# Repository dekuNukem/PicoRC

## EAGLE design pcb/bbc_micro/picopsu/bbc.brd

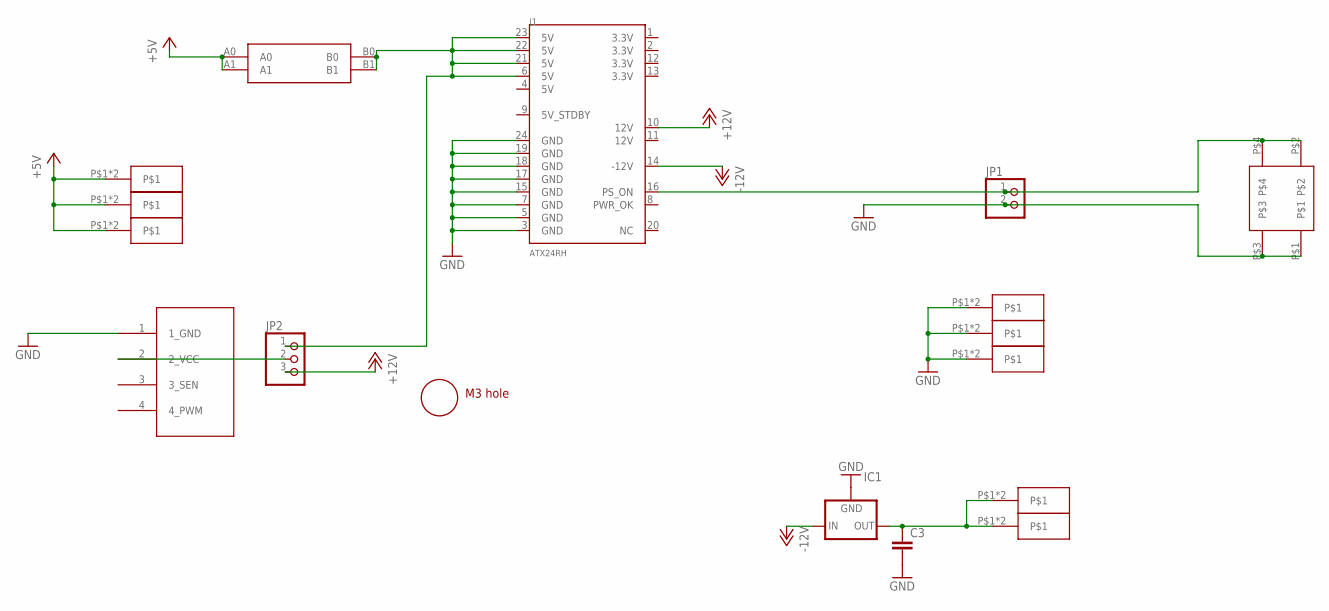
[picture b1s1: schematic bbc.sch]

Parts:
C3: C5/2.5; C5B2.5
IC1: 79XXS
J1: ATX24RH; ATX24_RIGHT_ANGLE
JP1: PINHD-1X2; 1X02
JP2: PINHD-1X3; 1X03
JP3: 4PIN_FAN; 1X04
U$1: CAR_FUSE_HOLDER3IN1; FUSE_HOLDER_3IN1
U$2, U$5, U$6, U$7, U$8, U$9, U$10, U$11: BLADE28; 2.8BLADE
U$3: ROCK_SW; ROCK_SWITCH
U$4: M3_MOUNTING_HOLE; M3_MOUNTING_HOLE_PACK

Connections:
+5V: U$1.A0, U$1.A1, U$6.P$1, U$6.P$2, U$7.P$1, U$7.P$2, U$8.P$1, U$8.P$2
+12V: J1.10 (12V), JP2.3
-12V: IC1.IN, J1.14 (-12V)
GND: C3.2, IC1.GND, J1.3 (GND), J1.5 (GND), J1.7 (GND), J1.15 (GND), J1.17 (GND), J1.18 (GND), J1.19 (GND), J1.24 (GND), JP1.2, JP3.1 (1_GND), U$3.P$1, U$3.P$3, U$9.P$1, U$9.P$2, U$10.P$1, U$10.P$2, U$11.P$1, U$11.P$2
unnamed: JP2.2, JP3.2 (2_VCC)
unnamed: C3.1, IC1.OUT, U$2.P$1, U$2.P$2, U$5.P$1, U$5.P$2
unnamed: J1.16 (PS_ON), JP1.1, U$3.P$2, U$3.P$4
unnamed: J1.6 (5V), J1.21 (5V), J1.22 (5V), J1.23 (5V), JP2.1, U$1.B0, U$1.B1

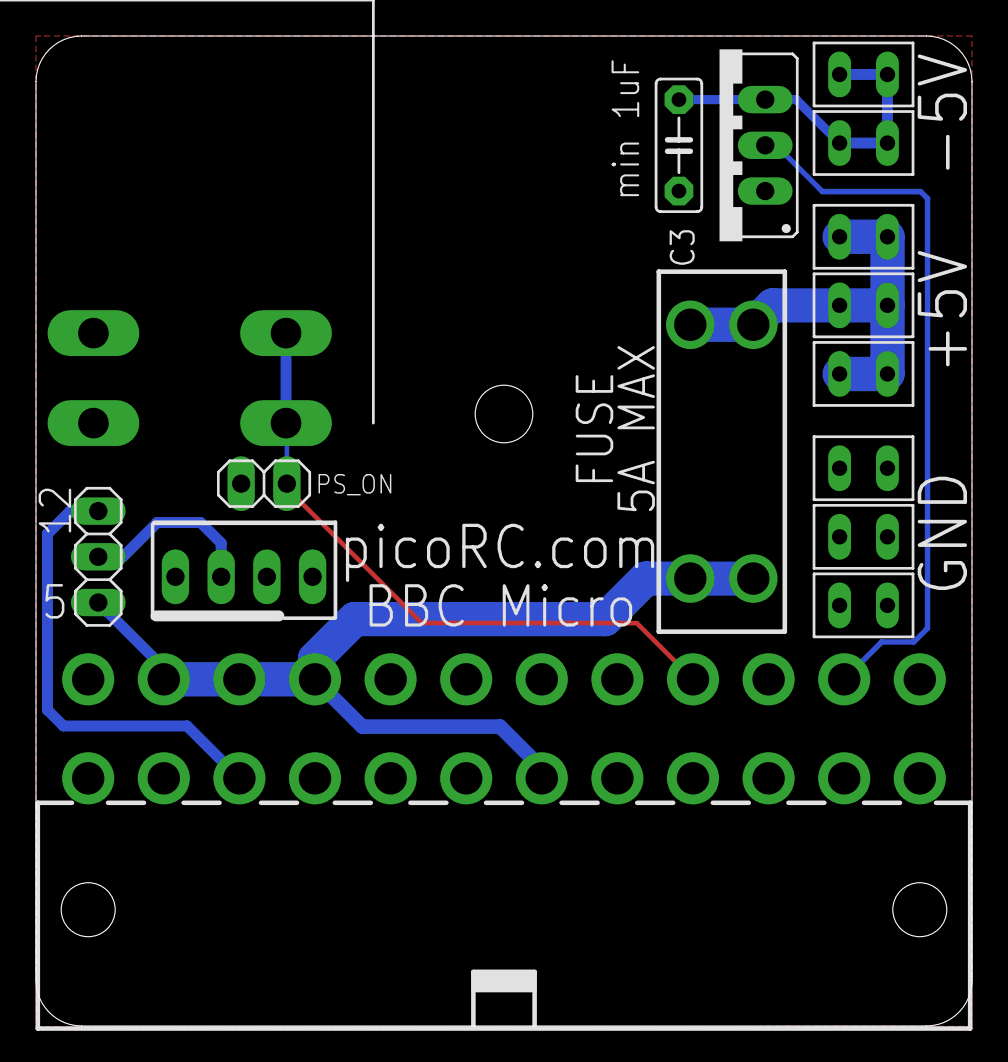
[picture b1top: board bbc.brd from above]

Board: 2 copper layers, 52.0 x 55.0 mm, 17 parts (0 on the bottom side), 8 nets.

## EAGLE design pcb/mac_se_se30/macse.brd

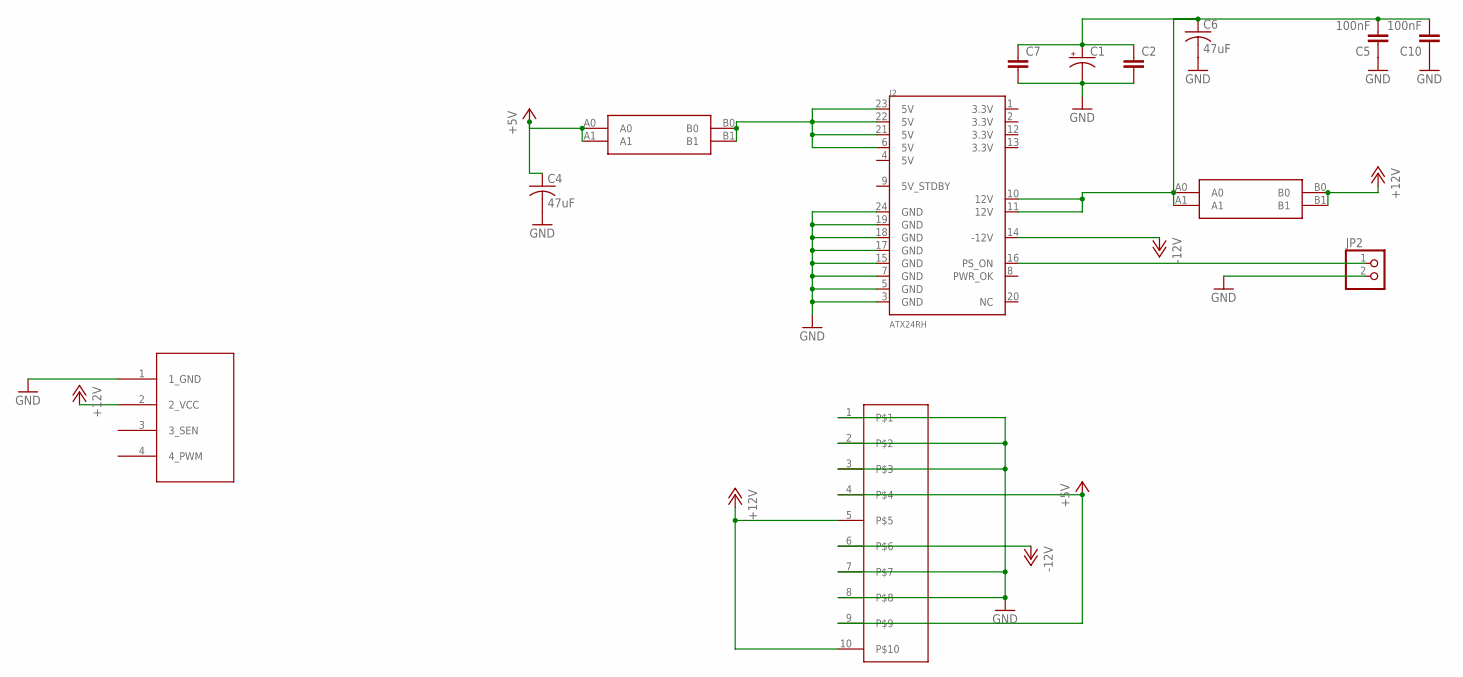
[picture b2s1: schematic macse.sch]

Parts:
C1: CPOL-USE3.5-8; E3,5-8
C2, C7: C5/2.5; C5B2.5
C4, C6: 47uF; C1210
C5, C10: 100nF; 0805@1
J2: ATX24RH; ATX24_RIGHT_ANGLE
JP2: PINHD-1X2/90; 1X02/90
JP3: 4PIN_FAN; 1X04
U$1: MACSE; MACSE_10P_STRAIGHT
U$2, U$8: CAR_FUSE_HOLDER3IN1; FUSE_HOLDER_3IN1

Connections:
+5V: C4.1, U$1.4, U$1.9, U$8.A0, U$8.A1
+12V: JP3.2 (2_VCC), U$1.5, U$1.10, U$2.B0, U$2.B1
-12V: J2.14 (-12V), U$1.6
GND: C1.-, C2.2, C4.2, C5.1, C6.2, C7.2, C10.1, J2.3 (GND), J2.5 (GND), J2.7 (GND), J2.15 (GND), J2.17 (GND), J2.18 (GND), J2.19 (GND), J2.24 (GND), JP2.2, JP3.1 (1_GND), U$1.1, U$1.2, U$1.3, U$1.7, U$1.8
unnamed: J2.16 (PS_ON), JP2.1
unnamed: J2.6 (5V), J2.21 (5V), J2.22 (5V), J2.23 (5V), U$8.B0, U$8.B1
unnamed: C1.+, C2.1, C5.2, C6.1, C7.1, C10.2, J2.10 (12V), J2.11 (12V), U$2.A0, U$2.A1

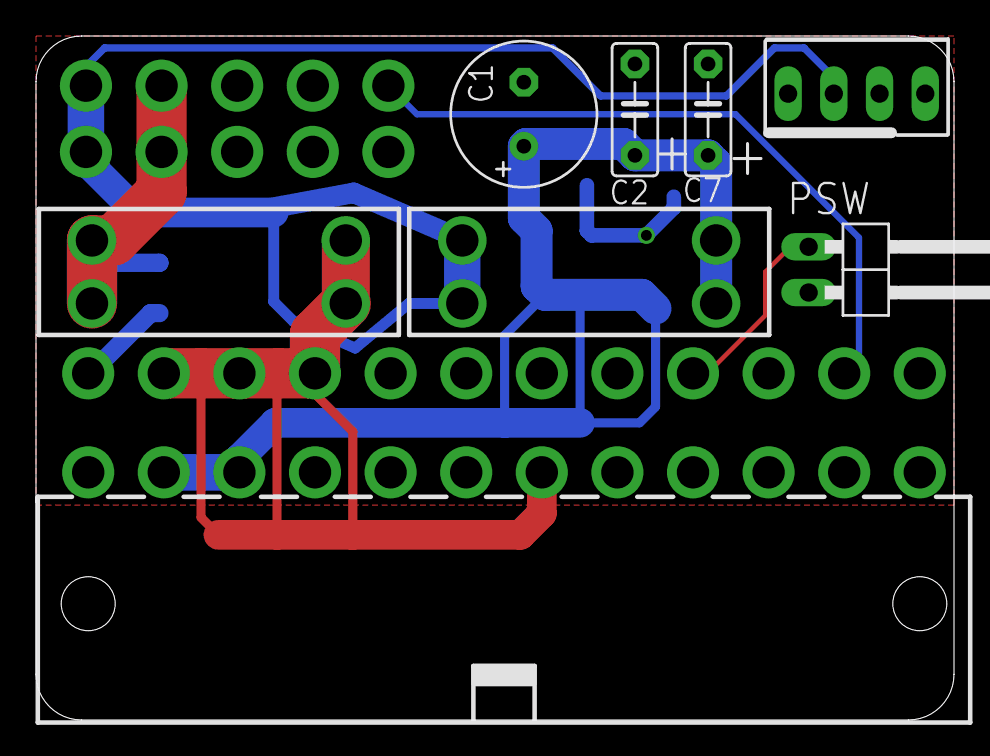
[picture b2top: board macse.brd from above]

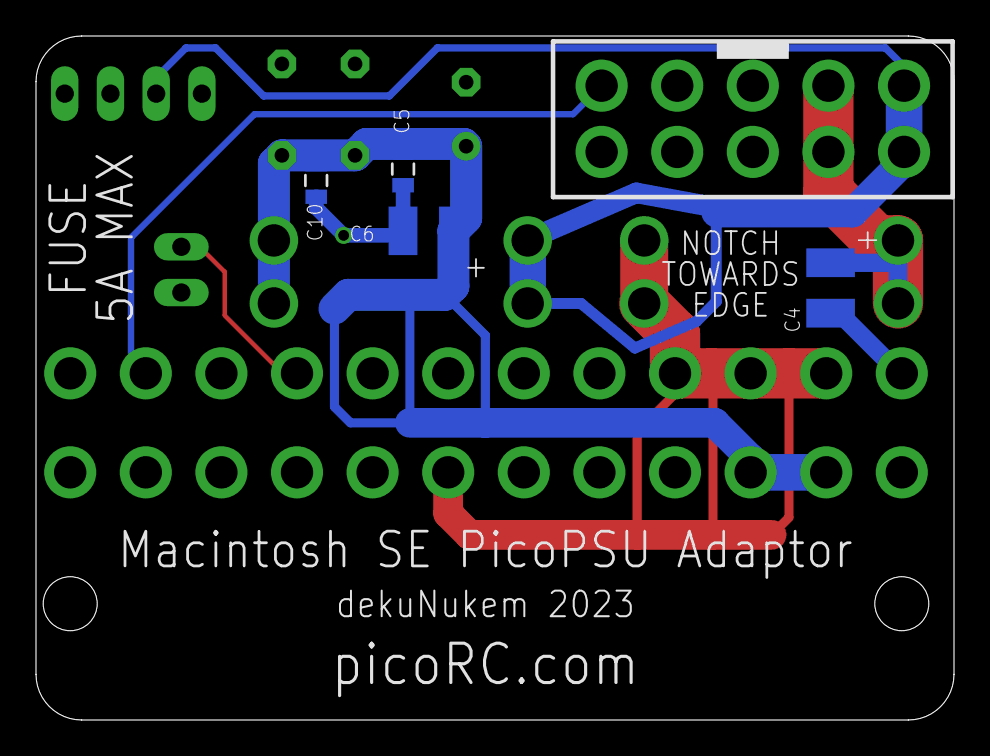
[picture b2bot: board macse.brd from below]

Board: 2 copper layers, 51.0 x 38.0 mm, 13 parts (4 on the bottom side), 7 nets.

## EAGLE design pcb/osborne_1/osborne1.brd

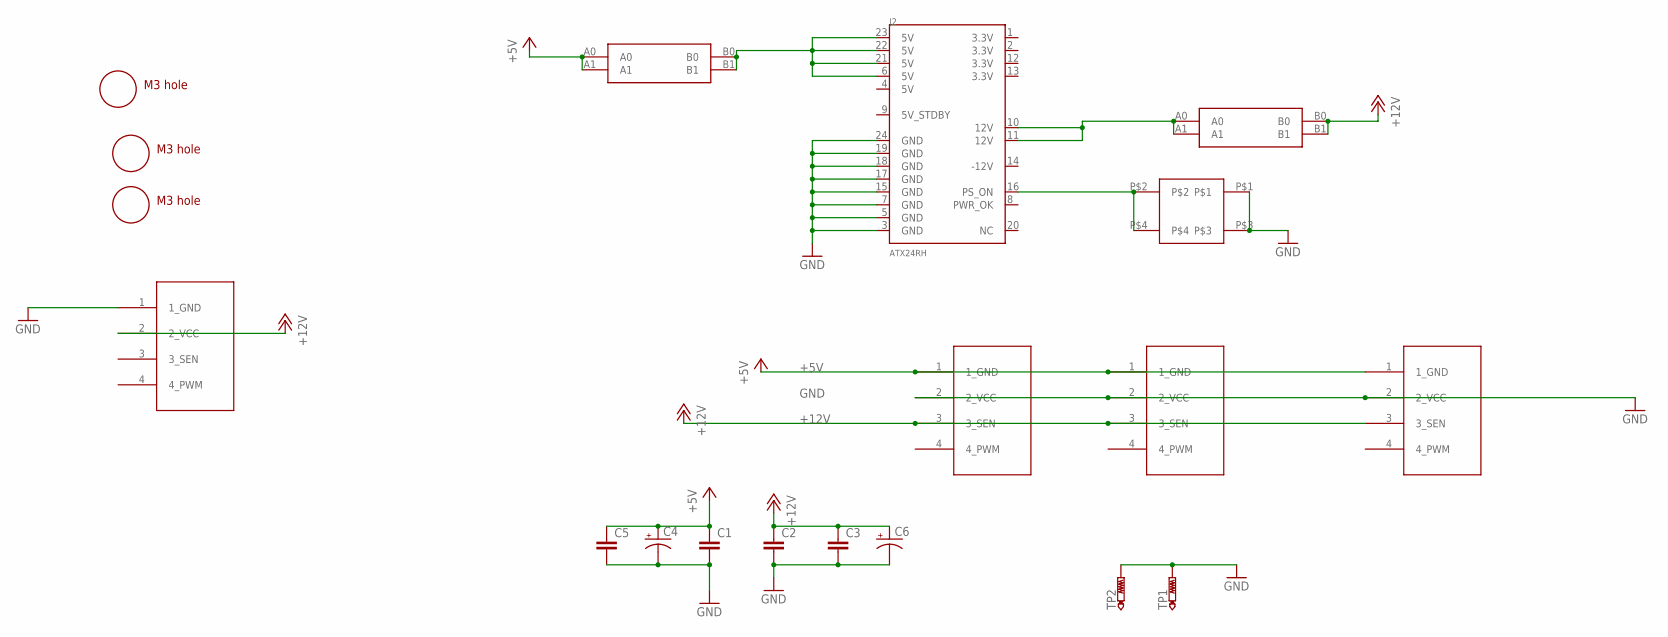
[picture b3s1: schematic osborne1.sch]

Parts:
C1, C2, C3, C5: C5/2.5; C5B2.5
C4, C6: CPOL-USE3.5-8; E3,5-8
J2: ATX24RH; ATX24_RIGHT_ANGLE
JP1, JP2, JP3, JP5: 4PIN_FAN; 1X04
TP1, TP2: PTR1PAD1-17; P1-17
U$1, U$3, U$5: M3_MOUNTING_HOLE; M3_MOUNTING_HOLE_PACK
U$2, U$8: CAR_FUSE_HOLDER3IN1; FUSE_HOLDER_3IN1
U$4: ROCK_SWRSW_VERTICAL; ROCK_SWITCH_VERTICAL

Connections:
+5V: C1.1, C4.+, C5.1, JP1.1 (1_GND), JP2.1 (1_GND), JP5.1 (1_GND), U$8.A0, U$8.A1
+12V: C2.1, C3.1, C6.+, JP1.3 (3_SEN), JP2.3 (3_SEN), JP3.2 (2_VCC), JP5.3 (3_SEN), U$2.B0, U$2.B1
GND: C1.2, C2.2, C3.2, C4.-, C5.2, C6.-, J2.3 (GND), J2.5 (GND), J2.7 (GND), J2.15 (GND), J2.17 (GND), J2.18 (GND), J2.19 (GND), J2.24 (GND), JP1.2 (2_VCC), JP2.2 (2_VCC), JP3.1 (1_GND), JP5.2 (2_VCC), TP1.TP, TP2.TP, U$4.P$1, U$4.P$3
unnamed: J2.16 (PS_ON), U$4.P$2, U$4.P$4
unnamed: J2.6 (5V), J2.21 (5V), J2.22 (5V), J2.23 (5V), U$8.B0, U$8.B1
unnamed: J2.10 (12V), J2.11 (12V), U$2.A0, U$2.A1

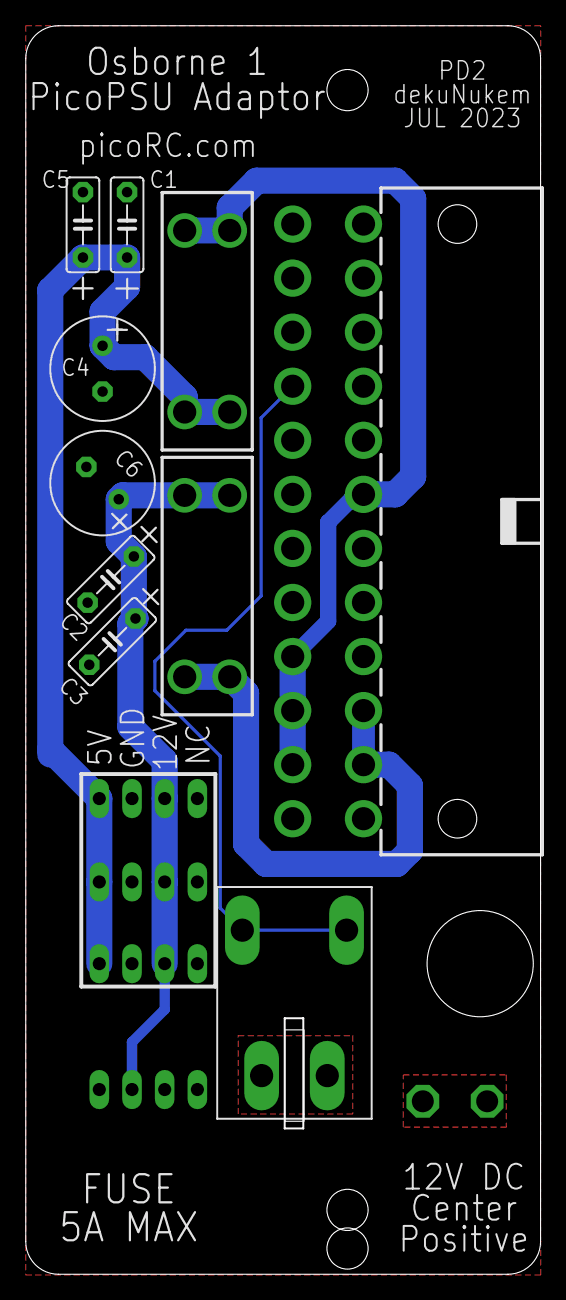
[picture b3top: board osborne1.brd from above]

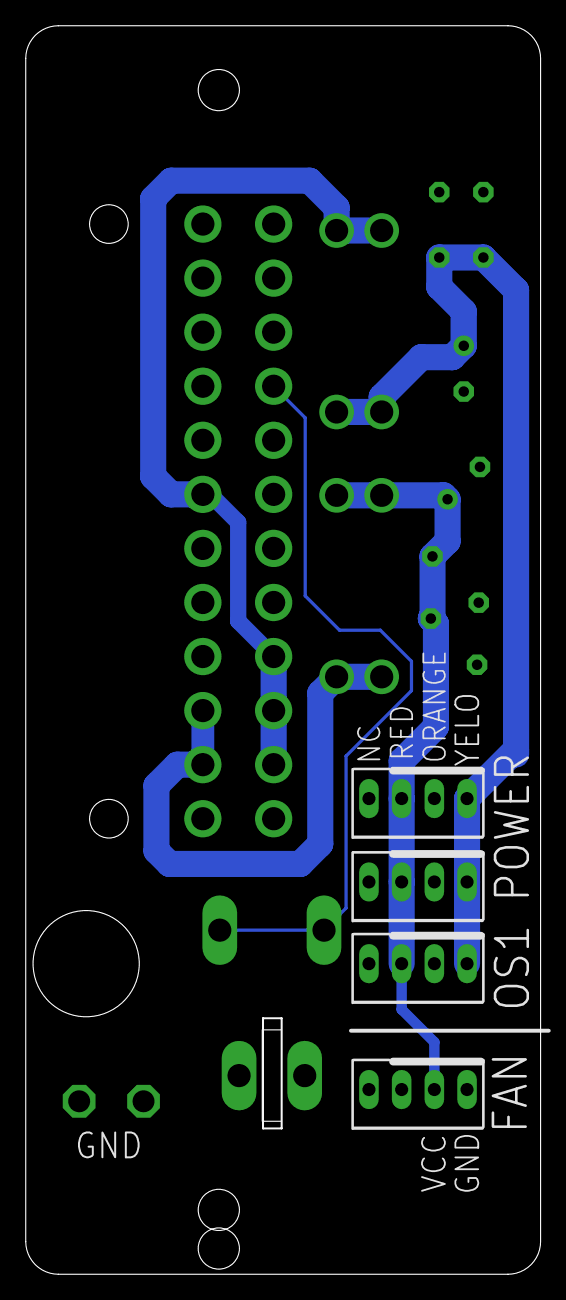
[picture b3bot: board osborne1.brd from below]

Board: 2 copper layers, 40.0 x 97.0 mm, 19 parts (4 on the bottom side), 6 nets.

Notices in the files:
parts and their libraries:
SparkFun-Connectors: Licensing: Creative Commons ShareAlike 4.0 International - https://creativecommons.org/licenses/by-sa/4.0
